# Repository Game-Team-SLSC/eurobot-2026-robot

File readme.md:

# Game Team's Eurobot 2026 Robot

## Hardware

### Architecture Diagram

```mermaid
graph LR
    %% SOURCES EXTERNES
    Batt((Batterie LiPo 4S))
    BAU[Bouton AU]

    %% PCB 1: LOGIC BOARD
    subgraph LB [Logic Board]
        direction TB
        MCU[ESP32-S3]
        Radio[Module Radio]
        Screen[Écran LCD]
        MCU --- Radio
        MCU --- Screen
    end

    %% PCB 2: POWER BOARD
    subgraph PB [Power Board]
        direction TB
        Prot[Protection Batterie]
        subgraph Drivers [Drivers Steppers]
            D_4x[4x Drivers]
        end
    end

    %% PCB 3: SERVO REGULATORS (Considéré comme un bloc PCB)
    subgraph Regs [Regulators Board]
        direction TB
        SR[2x 200W Servos]
        PR[1x 200W Pump Reg]
        Fan[1x Ventilateur]
    end

    %% PCB 4: ARM BOARD
    subgraph AB [Arm Board]
        direction TB
        PCA[3x PCA9685]
        Mos[4x MOSFET Pumps]
    end

    %% MATÉRIEL PHYSIQUE (Hors PCB)
    subgraph Mecanique [Éléments Mécaniques]
        Mots[4x Steppers]
        CN[Chasse-Neige]
        Bras[Bras & Pompes]
    end

    %% CONNEXIONS INTER-PCB (Puissance)
    Batt == "16.8V" ==> PB
    PB == "16.8V" ==> LB
    PB == "16.8V" ==> Regs
    Regs == "7V / 12V" ==> AB
    BAU -.-> PB
    AB -- PWM -->Regs

    %% CONNEXIONS INTER-PCB (Signaux)
    LB -- "SPI" --> PB
    LB -- "I2C Main" --> AB
    PB -- "Télémétrie" --> LB

    %% CONNEXIONS PCB VERS MÉCANIQUE
    PB == "Phases" ==> Mots
    AB -- "PWM" --> CN
    AB -- "Faisceau" --> Bras

    %% STYLES
    style LB fill:#f3e5f5,stroke:#7b1fa2,stroke-width:2px
    style PB fill:#fff9c4,stroke:#fbc02d,stroke-width:2px
    style Regs fill:#e1f5fe,stroke:#0288d1,stroke-width:2px
    style AB fill:#e8f5e9,stroke:#2e7d32,stroke-width:2px
```

### Power PCB

### Kinetic PCB

### Logic PCB

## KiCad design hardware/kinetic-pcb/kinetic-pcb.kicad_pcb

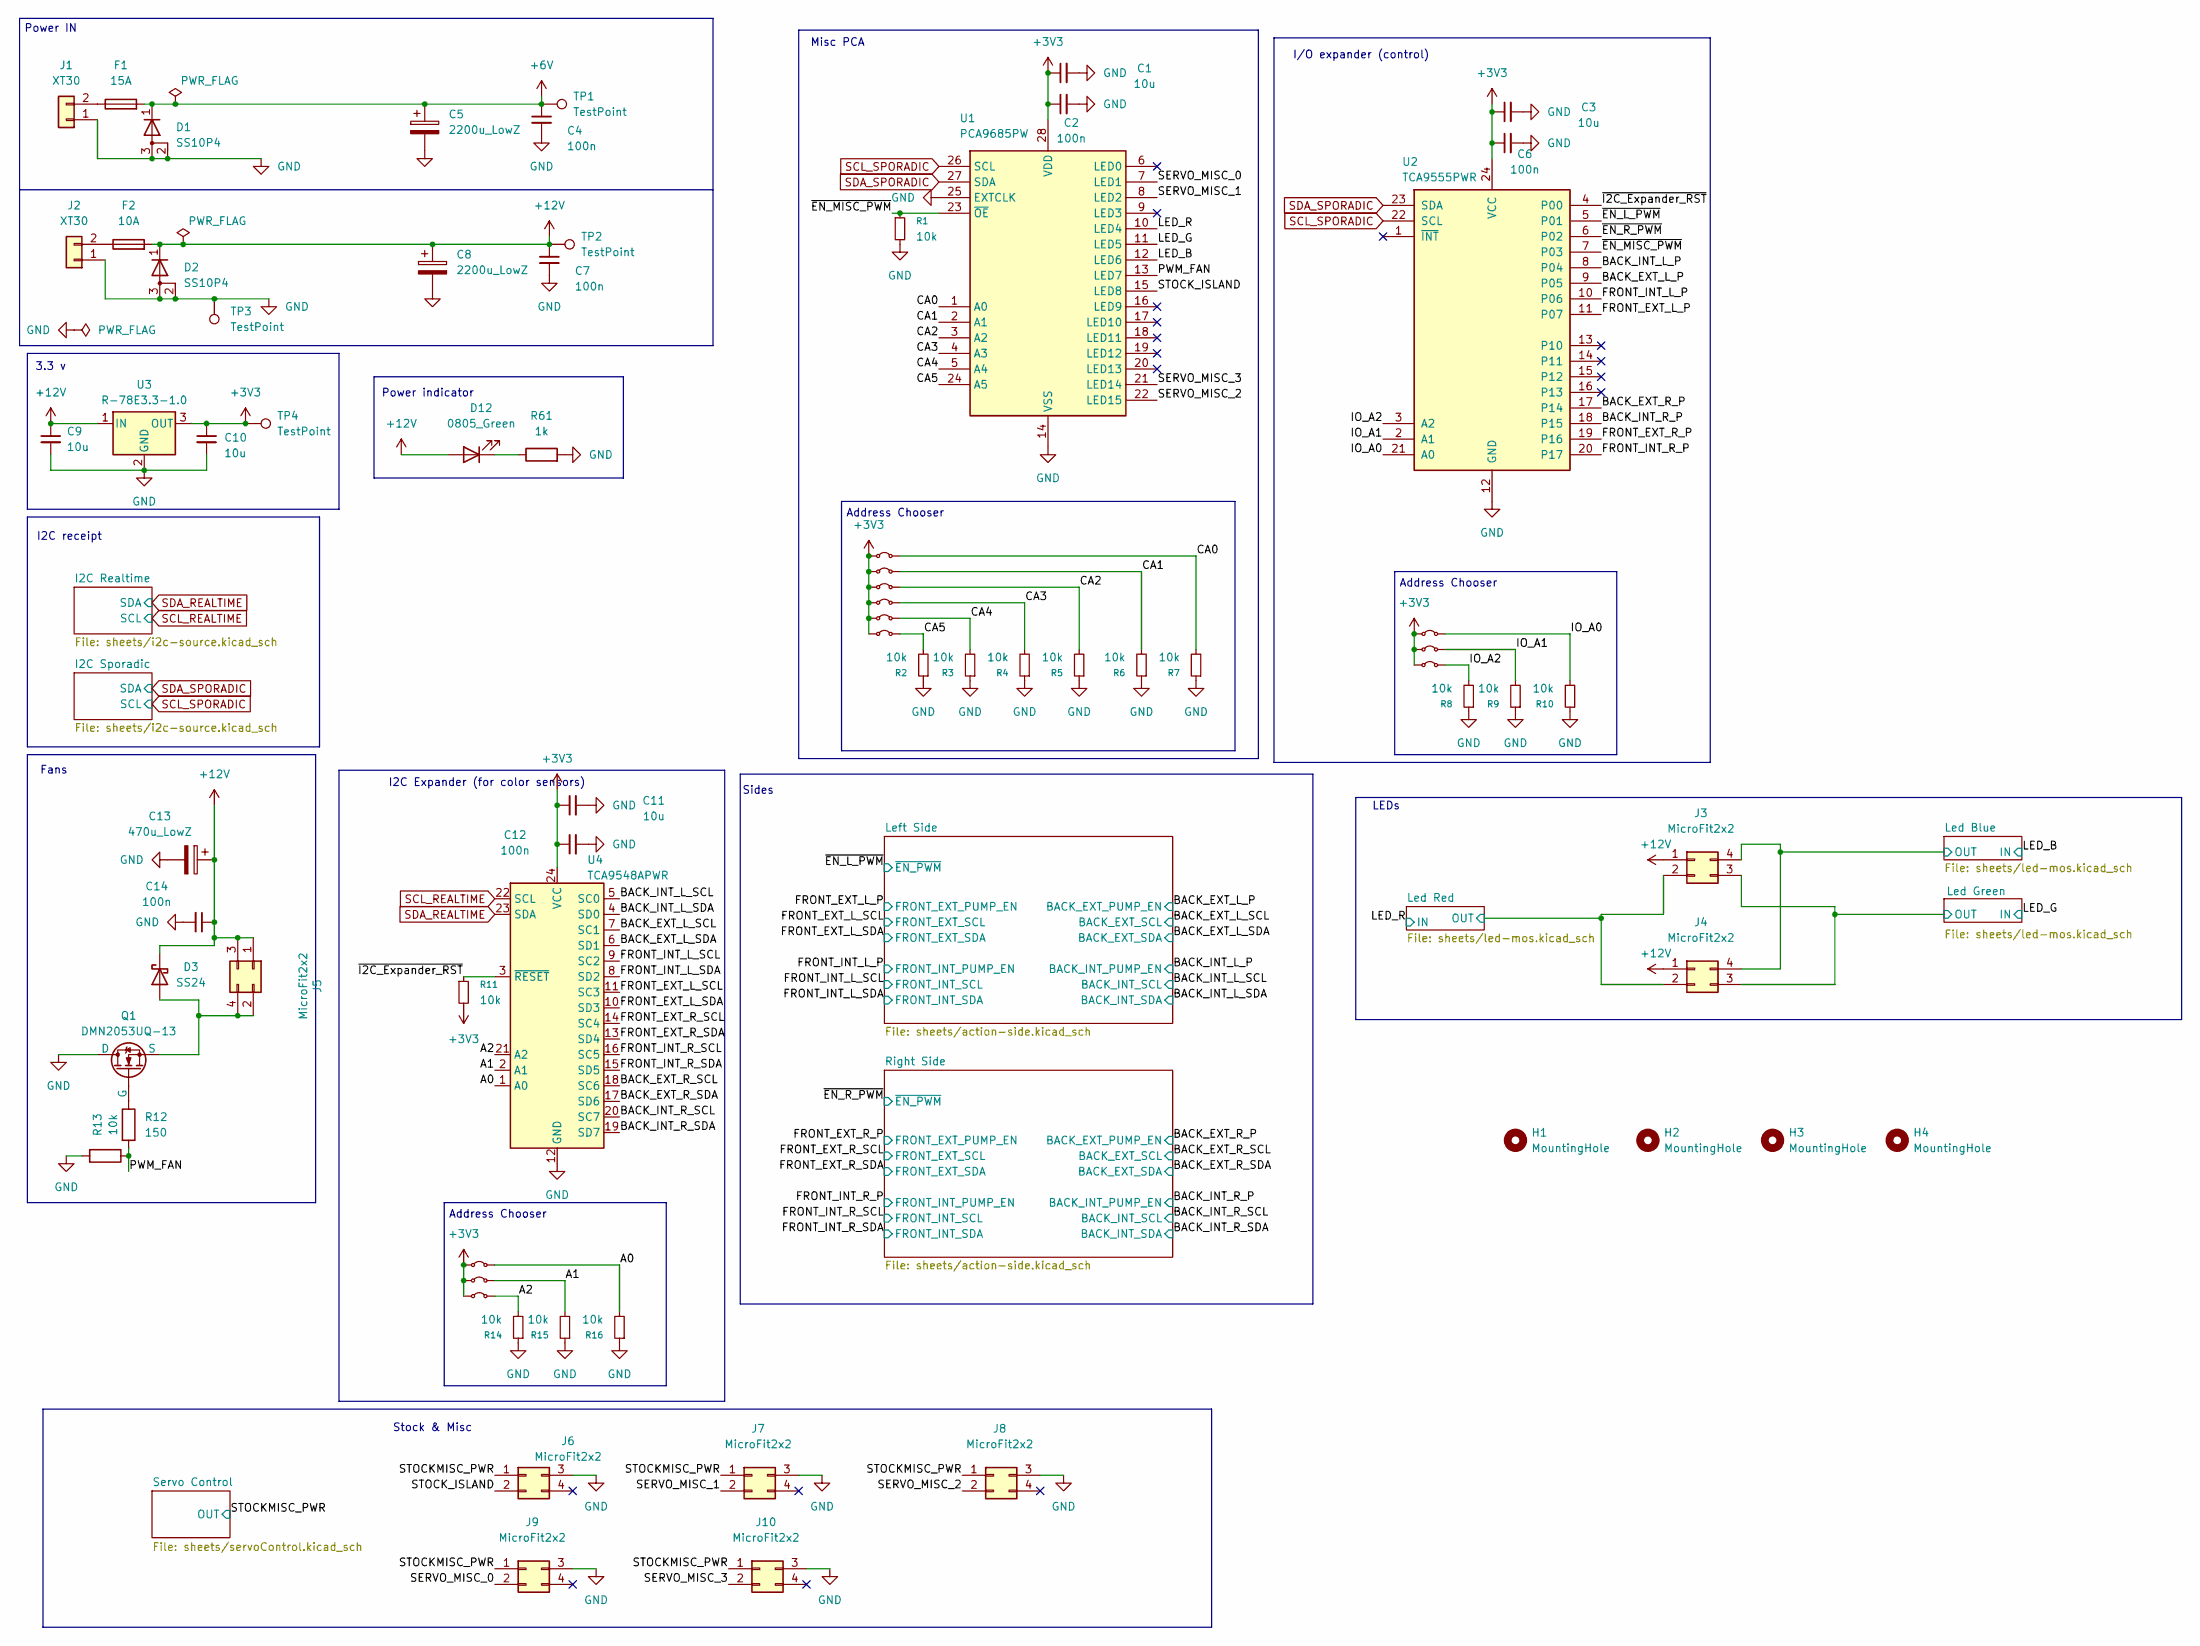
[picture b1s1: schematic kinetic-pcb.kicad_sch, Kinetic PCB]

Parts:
C1, C3, C9, C10, C11: 10u; C_0805_2012Metric_Pad1.18x1.45mm_HandSolder; MPN CL21A106KBYQNNE
C2, C4, C6, C7, C12, C14: 100n; C_0805_2012Metric_Pad1.18x1.45mm_HandSolder; MPN CL21B104KBCNNND
C5, C8: 2200u_LowZ; CP_Radial_D16.0mm_P7.50mm; MPN EEUFR1V222
C13: 470u_LowZ; CP_Radial_D10.0mm_P5.00mm; MPN EEU-FR1E471
D1, D2: SS10P4; SS10P4M387A; MPN SS10P4-M3/87A
D3: SS24; D_SMA_Handsoldering; MPN SS24S-E3/5AT
D12: 0805_Green; LED_0805_2012Metric_Pad1.15x1.40mm_HandSolder; MPN APA2106ZGCK
F1: 15A; Fuseholder_Cylinder-5x20mm_Schurter_0031_8201_Horizontal_Op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
F2: 10A; Fuseholder_Cylinder-5x20mm_Schurter_0031_8201_Horizontal_Op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
H1, H2, H3, H4: MountingHole; MountingHole_3.2mm_M3
J1, J2: XT30; AMASS_XT30U-M_1x02_P5.0mm_Vertical
J3, J4, J5, J6, J7, J8, J9, J10: MicroFit2x2; J_Wurth_WR-MPC3_66200421122; MPN 66200421122
NT1, NT2, NT3, NT4, NT5, NT6, NT7, NT8, NT9, NT10, NT11, NT12: Jumper_2_Bridged; TestPoint_2Pads_Pitch2.54mm_Drill0.8mm; MPN M7582-46
Q1: DMN2053UQ-13; SOT-23_Handsoldering-DMN2053UQ; MPN DMN2053UQ-13
R1, R2, R3, R4, R5, R6, R7, R8, R9, R10, R11, R13, R14, R15, R16: 10k; R_0805_2012Metric_Pad1.20x1.40mm_HandSolder; MPN CRCW080510K0FKEA
R12: 150; R_0805_2012Metric_Pad1.20x1.40mm_HandSolder; MPN CRCW0805150RFKEA
R61: 1k; R_0805_2012Metric_Pad1.20x1.40mm_HandSolder; MPN CRCW08051K00FKEA
TP1, TP2, TP3, TP4: TestPoint; TestPoint_THTPad_D2.0mm_Drill1.0mm
U1: PCA9685PW; TSSOP-28_4.4x9.7mm_P0.65mm; MPN PCA9685PW,118
U2: TCA9555PWR; TSSOP-24_4.4x7.8mm_P0.65mm; MPN TCA9555PWR
U3: R-78E3.3-1.0; Converter_DCDC_RECOM_R-78E-0.5_THT; MPN R-78E3.3-1.0
U4: TCA9548APWR; TSSOP-24_4.4x7.8mm_P0.65mm; MPN TCA9548APWR

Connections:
+3V3: C1.1, C2.1, C3.1, C6.1, C10.1, C11.1, C12.1, NT1.1 (A), NT2.1 (A), NT3.1 (A), NT4.1 (A), NT5.1 (A), NT6.1 (A), NT7.1 (A), NT8.1 (A), NT9.1 (A), NT10.1 (A), NT11.1 (A), NT12.1 (A), R11.2, TP4.1, U1.28 (VDD), U2.24 (VCC), U3.3 (OUT), U4.24 (VCC); also elsewhere on the board
+6V: C4.1, C5.1, D1.1 (K), F1.2, J6.1, J7.1, J8.1, J9.1, J10.1, TP1.1; also elsewhere on the board
+12V: C7.1, C8.1, C9.1, C13.1, C14.1, D2.1 (K), D3.1 (K), D12.2 (A), F2.2, J3.1, J4.1, J5.1, J5.3, TP2.1, U3.1 (IN); also elsewhere on the board
/A0: NT10.2 (B), R16.2, U4.1 (A0)
/A1: NT11.2 (B), R15.2, U4.2 (A1)
/A2: NT12.2 (B), R14.2, U4.21 (A2)
/BACK_EXT_L_P: U2.9 (P05); also elsewhere on the board
/BACK_EXT_L_SCL: U4.7 (SC1); also elsewhere on the board
/BACK_EXT_L_SDA: U4.6 (SD1); also elsewhere on the board
/BACK_EXT_R_P: U2.17 (P14); also elsewhere on the board
/BACK_EXT_R_SCL: U4.18 (SC6); also elsewhere on the board
/BACK_EXT_R_SDA: U4.17 (SD6); also elsewhere on the board
/BACK_INT_L_P: U2.8 (P04); also elsewhere on the board
/BACK_INT_L_SCL: U4.5 (SC0); also elsewhere on the board
/BACK_INT_L_SDA: U4.4 (SD0); also elsewhere on the board
/BACK_INT_R_P: U2.18 (P15); also elsewhere on the board
/BACK_INT_R_SCL: U4.20 (SC7); also elsewhere on the board
/BACK_INT_R_SDA: U4.19 (SD7); also elsewhere on the board
/CA0: NT1.2 (B), R7.2, U1.1 (A0)
/CA1: NT2.2 (B), R6.2, U1.2 (A1)
/CA2: NT3.2 (B), R5.2, U1.3 (A2)
/CA3: NT4.2 (B), R4.2, U1.4 (A3)
/CA4: NT5.2 (B), R3.2, U1.5 (A4)
/CA5: NT6.2 (B), R2.2, U1.24 (A5)
/FRONT_EXT_L_P: U2.11 (P07); also elsewhere on the board
/FRONT_EXT_L_SCL: U4.11 (SC3); also elsewhere on the board
/FRONT_EXT_L_SDA: U4.10 (SD3); also elsewhere on the board
/FRONT_EXT_R_P: U2.19 (P16); also elsewhere on the board
/FRONT_EXT_R_SCL: U4.14 (SC4); also elsewhere on the board
/FRONT_EXT_R_SDA: U4.13 (SD4); also elsewhere on the board
/FRONT_INT_L_P: U2.10 (P06); also elsewhere on the board
/FRONT_INT_L_SCL: U4.9 (SC2); also elsewhere on the board
/FRONT_INT_L_SDA: U4.8 (SD2); also elsewhere on the board
/FRONT_INT_R_P: U2.20 (P17); also elsewhere on the board
/FRONT_INT_R_SCL: U4.16 (SC5); also elsewhere on the board
/FRONT_INT_R_SDA: U4.15 (SD5); also elsewhere on the board
/IO_A0: NT7.2 (B), R10.2, U2.21 (A0)
/IO_A1: NT8.2 (B), R9.2, U2.2 (A1)
/IO_A2: NT9.2 (B), R8.2, U2.3 (A2)
/LED_B: U1.12 (LED6); also elsewhere on the board
/LED_G: U1.11 (LED5); also elsewhere on the board
/LED_R: U1.10 (LED4); also elsewhere on the board
/Led Blue/OUT: J3.4, J4.4; also elsewhere on the board
/Led Green/OUT: J3.3, J4.3; also elsewhere on the board
/Led Red/OUT: J3.2, J4.2; also elsewhere on the board
/PWM_FAN: R12.2, R13.1, U1.13 (LED7)
/SERVO_MISC_0: J9.2, U1.7 (LED1)
/SERVO_MISC_1: J7.2, U1.8 (LED2)
/SERVO_MISC_2: J8.2, U1.22 (LED15)
/SERVO_MISC_3: J10.2, U1.21 (LED14)
/STOCK_ISLAND: J6.2, U1.15 (LED8)
/~EN_L_PWM: U2.5 (P01); also elsewhere on the board
/~EN_MISC_PWM: R1.1, U1.23 (~OE), U2.7 (P03)
/~EN_R_PWM: U2.6 (P02); also elsewhere on the board
/~I2C_Expander_RST: R11.1, U2.4 (P00), U4.3 (~RESET)
GND: C1.2, C2.2, C3.2, C4.2, C5.2, C6.2, C7.2, C8.2, C9.2, C10.2, C11.2, C12.2, C13.2, C14.2, D1.2 (A), D1.3 (A), D2.2 (A), D2.3 (A), J1.1, J2.1, J6.3, J7.3, J8.3, J9.3, J10.3, Q1.1 (D), R1.2, R2.1, R3.1, R4.1, R5.1, R6.1, R7.1, R8.1, R9.1, R10.1, R13.2, R14.1, R15.1, R16.1, R61.2, TP3.1, U1.14 (VSS), U1.25 (EXTCLK), U2.12 (GND), U3.2 (GND), U4.12 (GND); also elsewhere on the board
unnamed: D3.2 (A), J5.2, J5.4, Q1.3 (S)
unnamed: D12.1 (K), R61.1
unnamed: F1.1, J1.2
unnamed: F2.1, J2.2
unnamed: Q1.2 (G), R12.1
SCL_REALTIME: U4.22 (SCL); also elsewhere on the board
SCL_SPORADIC: U1.26 (SCL), U2.22 (SCL); also elsewhere on the board
SDA_REALTIME: U4.23 (SDA); also elsewhere on the board
SDA_SPORADIC: U1.27 (SDA), U2.23 (SDA); also elsewhere on the board

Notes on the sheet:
Fans
Address Chooser
3.3 v
Sides
I2C Expander (for color sensors)
Stock & Misc
Power IN
Power indicator
I/O expander (control)
LEDs
Misc PCA
I2C receipt

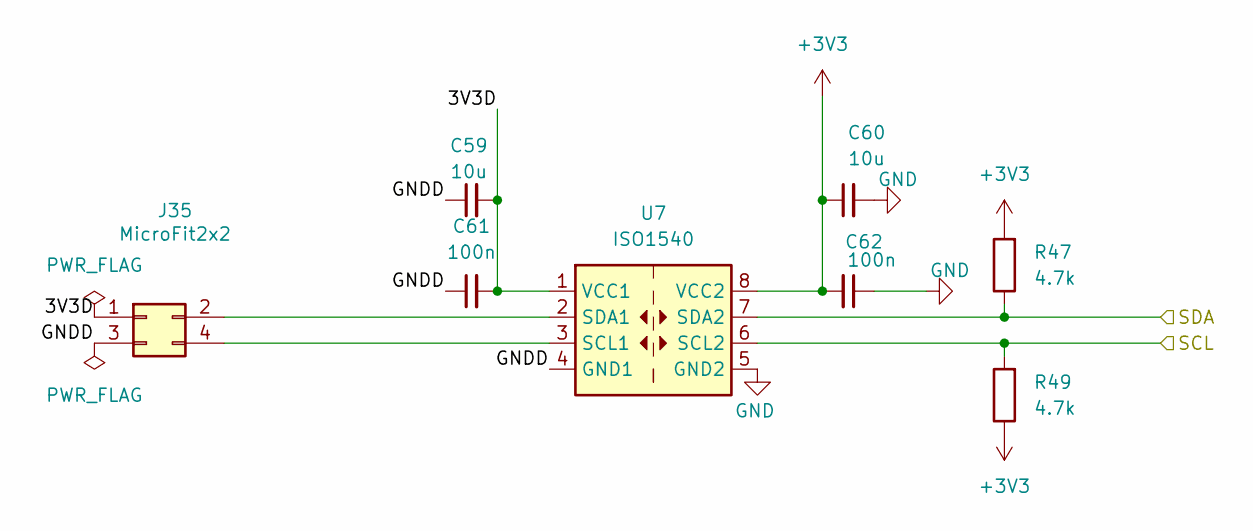
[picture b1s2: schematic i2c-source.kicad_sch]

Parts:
C59, C60: 10u; C_0805_2012Metric_Pad1.18x1.45mm_HandSolder; MPN CL21A106KBYQNNE
C61, C62: 100n; C_0805_2012Metric_Pad1.18x1.45mm_HandSolder; MPN CL21B104KBCNNND
J35: MicroFit2x2; J_Wurth_WR-MPC3_66200421122; MPN 66200421122
R47, R49: 4.7k; R_0805_2012Metric_Pad1.20x1.40mm_HandSolder; MPN CRCW08054K70FKEA
U7: ISO1540; SOIC-8_3.9x4.9mm_P1.27mm; MPN ISO1540DR

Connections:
+3V3: C60.1, C62.2, R47.2, R49.1, U7.8 (VCC2); also elsewhere on the board
/I2C Sporadic/3V3D: C59.2, C61.2, J35.1, U7.1 (VCC1)
/I2C Sporadic/GNDD: C59.1, C61.1, J35.3, U7.4 (GND1)
GND: C60.2, C62.1, U7.5 (GND2); also elsewhere on the board
unnamed: J35.2, U7.2 (SDA1)
unnamed: J35.4, U7.3 (SCL1)
SCL_SPORADIC: R49.2, U7.6 (SCL2); also elsewhere on the board
SDA_SPORADIC: R47.1, U7.7 (SDA2); also elsewhere on the board

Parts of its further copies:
C63, C64: 10u; C_0805_2012Metric_Pad1.18x1.45mm_HandSolder; MPN CL21A106KBYQNNE
C65, C66: 100n; C_0805_2012Metric_Pad1.18x1.45mm_HandSolder; MPN CL21B104KBCNNND
J36: MicroFit2x2; J_Wurth_WR-MPC3_66200421122; MPN 66200421122
R54, R56: 4.7k; R_0805_2012Metric_Pad1.20x1.40mm_HandSolder; MPN CRCW08054K70FKEA
U8: ISO1540; SOIC-8_3.9x4.9mm_P1.27mm; MPN ISO1540DR

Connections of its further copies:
+3V3: C64.1, C66.2, R54.2, R56.1, U8.8 (VCC2); also elsewhere on the board
/I2C Realtime/3V3D: C63.2, C65.2, J36.1, U8.1 (VCC1)
/I2C Realtime/GNDD: C63.1, C65.1, J36.3, U8.4 (GND1)
GND: C64.2, C66.1, U8.5 (GND2); also elsewhere on the board
unnamed: J36.2, U8.2 (SDA1)
unnamed: J36.4, U8.3 (SCL1)
SCL_REALTIME: R56.2, U8.6 (SCL2); also elsewhere on the board
SDA_REALTIME: R54.1, U8.7 (SDA2); also elsewhere on the board

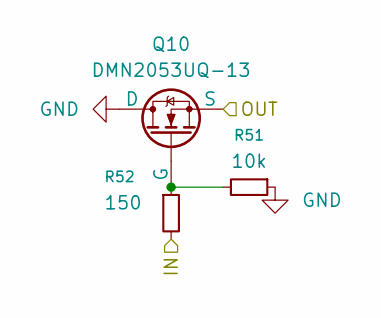
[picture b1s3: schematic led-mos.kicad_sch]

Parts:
Q10: DMN2053UQ-13; SOT-23_Handsoldering-DMN2053UQ; MPN DMN2053UQ-13
R51: 10k; R_0805_2012Metric_Pad1.20x1.40mm_HandSolder; MPN CRCW080510K0FKEA
R52: 150; R_0805_2012Metric_Pad1.20x1.40mm_HandSolder; MPN CRCW0805150RFKEA

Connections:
/LED_G: R52.2; also elsewhere on the board
/Led Green/OUT: Q10.3 (S); also elsewhere on the board
GND: Q10.1 (D), R51.1; also elsewhere on the board
unnamed: Q10.2 (G), R51.2, R52.1

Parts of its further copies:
Q11, Q12: DMN2053UQ-13; SOT-23_Handsoldering-DMN2053UQ; MPN DMN2053UQ-13
R57, R59: 10k; R_0805_2012Metric_Pad1.20x1.40mm_HandSolder; MPN CRCW080510K0FKEA
R58, R60: 150; R_0805_2012Metric_Pad1.20x1.40mm_HandSolder; MPN CRCW0805150RFKEA

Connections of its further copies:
/LED_B: R58.2; also elsewhere on the board
/LED_R: R60.2; also elsewhere on the board
/Led Blue/OUT: Q11.3 (S); also elsewhere on the board
/Led Red/OUT: Q12.3 (S); also elsewhere on the board
GND: Q11.1 (D), Q12.1 (D), R57.1, R59.1; also elsewhere on the board
unnamed: Q11.2 (G), R57.2, R58.1
unnamed: Q12.2 (G), R59.2, R60.1

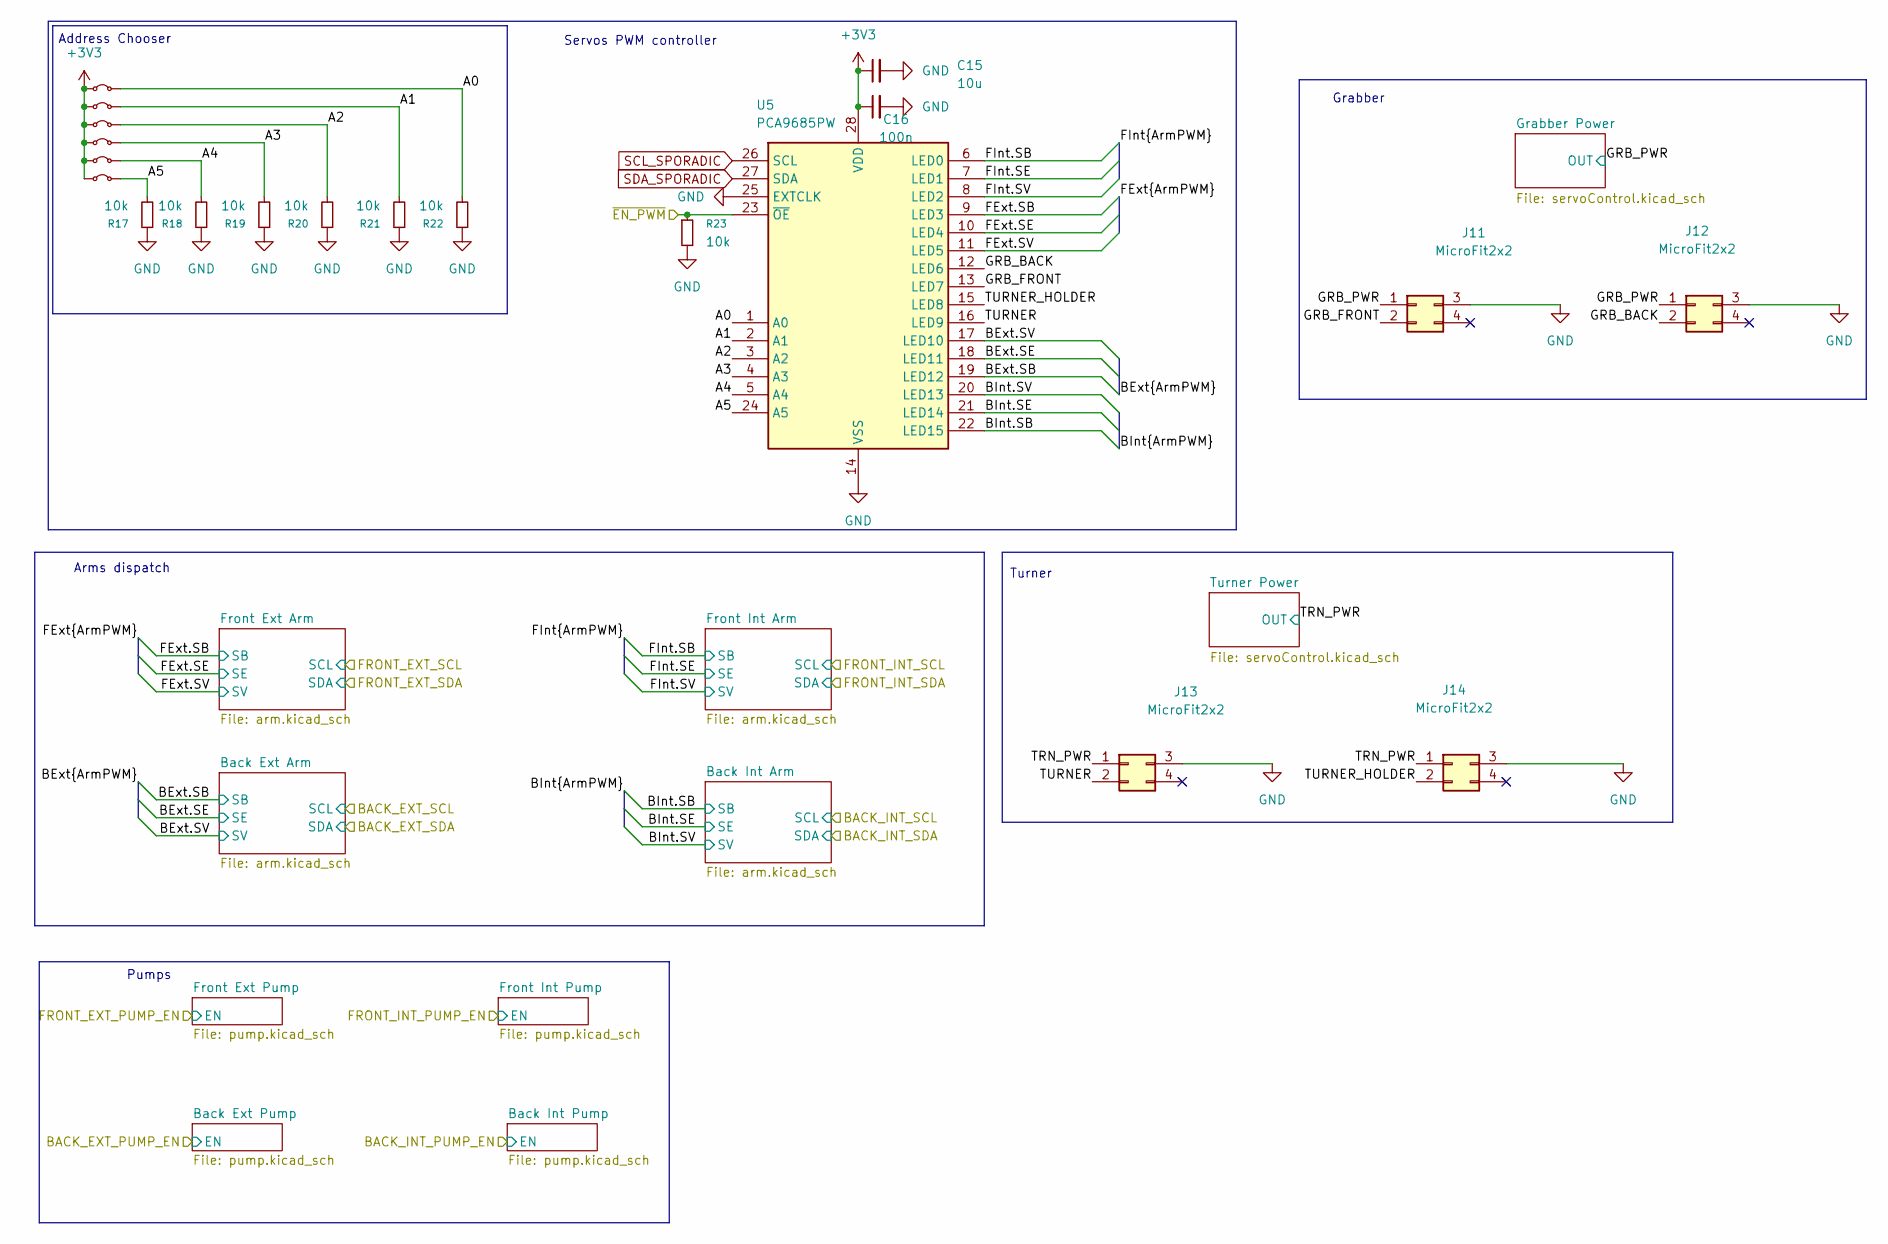
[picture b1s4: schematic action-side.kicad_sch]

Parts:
C15: 10u; C_0805_2012Metric_Pad1.18x1.45mm_HandSolder; MPN CL21A106KBYQNNE
C16: 100n; C_0805_2012Metric_Pad1.18x1.45mm_HandSolder; MPN CL21B104KBCNNND
J11, J12, J13, J14: MicroFit2x2; J_Wurth_WR-MPC3_66200421122; MPN 66200421122
NT13, NT14, NT15, NT16, NT17, NT18: Jumper_2_Bridged; TestPoint_2Pads_Pitch2.54mm_Drill0.8mm; MPN M7582-46
R17, R18, R19, R20, R21, R22, R23: 10k; R_0805_2012Metric_Pad1.20x1.40mm_HandSolder; MPN CRCW080510K0FKEA
U5: PCA9685PW; TSSOP-28_4.4x9.7mm_P0.65mm; MPN PCA9685PW,118

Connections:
+3V3: C15.1, C16.1, NT13.1 (A), NT14.1 (A), NT15.1 (A), NT16.1 (A), NT17.1 (A), NT18.1 (A), U5.28 (VDD); also elsewhere on the board
+6V: J11.1, J12.1, J13.1, J14.1; also elsewhere on the board
/Left Side/A0: NT13.2 (B), R22.2, U5.1 (A0)
/Left Side/A1: NT14.2 (B), R21.2, U5.2 (A1)
/Left Side/A2: NT15.2 (B), R20.2, U5.3 (A2)
/Left Side/A3: NT16.2 (B), R19.2, U5.4 (A3)
/Left Side/A4: NT17.2 (B), R18.2, U5.5 (A4)
/Left Side/A5: NT18.2 (B), R17.2, U5.24 (A5)
/Left Side/BExt.SB: U5.19 (LED12); also elsewhere on the board
/Left Side/BExt.SE: U5.18 (LED11); also elsewhere on the board
/Left Side/BExt.SV: U5.17 (LED10); also elsewhere on the board
/Left Side/BInt.SB: U5.22 (LED15); also elsewhere on the board
/Left Side/BInt.SE: U5.21 (LED14); also elsewhere on the board
/Left Side/BInt.SV: U5.20 (LED13); also elsewhere on the board
/Left Side/FExt.SB: U5.9 (LED3); also elsewhere on the board
/Left Side/FExt.SE: U5.10 (LED4); also elsewhere on the board
/Left Side/FExt.SV: U5.11 (LED5); also elsewhere on the board
/Left Side/FInt.SB: U5.6 (LED0); also elsewhere on the board
/Left Side/FInt.SE: U5.7 (LED1); also elsewhere on the board
/Left Side/FInt.SV: U5.8 (LED2); also elsewhere on the board
/Left Side/GRB_BACK: J12.2, U5.12 (LED6)
/Left Side/GRB_FRONT: J11.2, U5.13 (LED7)
/Left Side/TURNER: J13.2, U5.16 (LED9)
/Left Side/TURNER_HOLDER: J14.2, U5.15 (LED8)
/~EN_L_PWM: R23.1, U5.23 (~OE); also elsewhere on the board
GND: C15.2, C16.2, J11.3, J12.3, J13.3, J14.3, R17.1, R18.1, R19.1, R20.1, R21.1, R22.1, R23.2, U5.14 (VSS), U5.25 (EXTCLK); also elsewhere on the board
SCL_SPORADIC: U5.26 (SCL); also elsewhere on the board
SDA_SPORADIC: U5.27 (SDA); also elsewhere on the board

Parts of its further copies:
C21: 10u; C_0805_2012Metric_Pad1.18x1.45mm_HandSolder; MPN CL21A106KBYQNNE
C22: 100n; C_0805_2012Metric_Pad1.18x1.45mm_HandSolder; MPN CL21B104KBCNNND
J17, J18, J19, J20: MicroFit2x2; J_Wurth_WR-MPC3_66200421122; MPN 66200421122
NT19, NT20, NT21, NT22, NT23, NT24: Jumper_2_Bridged; TestPoint_2Pads_Pitch2.54mm_Drill0.8mm; MPN M7582-46
R26, R27, R28, R29, R30, R31, R32: 10k; R_0805_2012Metric_Pad1.20x1.40mm_HandSolder; MPN CRCW080510K0FKEA
U6: PCA9685PW; TSSOP-28_4.4x9.7mm_P0.65mm; MPN PCA9685PW,118

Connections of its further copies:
+3V3: C21.1, C22.1, NT19.1 (A), NT20.1 (A), NT21.1 (A), NT22.1 (A), NT23.1 (A), NT24.1 (A), U6.28 (VDD); also elsewhere on the board
+6V: J17.1, J18.1, J19.1, J20.1; also elsewhere on the board
/Right Side/A0: NT19.2 (B), R31.2, U6.1 (A0)
/Right Side/A1: NT20.2 (B), R30.2, U6.2 (A1)
/Right Side/A2: NT21.2 (B), R29.2, U6.3 (A2)
/Right Side/A3: NT22.2 (B), R28.2, U6.4 (A3)
/Right Side/A4: NT23.2 (B), R27.2, U6.5 (A4)
/Right Side/A5: NT24.2 (B), R26.2, U6.24 (A5)
/Right Side/BExt.SB: U6.19 (LED12); also elsewhere on the board
/Right Side/BExt.SE: U6.18 (LED11); also elsewhere on the board
/Right Side/BExt.SV: U6.17 (LED10); also elsewhere on the board
/Right Side/BInt.SB: U6.22 (LED15); also elsewhere on the board
/Right Side/BInt.SE: U6.21 (LED14); also elsewhere on the board
/Right Side/BInt.SV: U6.20 (LED13); also elsewhere on the board
/Right Side/FExt.SB: U6.9 (LED3); also elsewhere on the board
/Right Side/FExt.SE: U6.10 (LED4); also elsewhere on the board
/Right Side/FExt.SV: U6.11 (LED5); also elsewhere on the board
/Right Side/FInt.SB: U6.6 (LED0); also elsewhere on the board
/Right Side/FInt.SE: U6.7 (LED1); also elsewhere on the board
/Right Side/FInt.SV: U6.8 (LED2); also elsewhere on the board
/Right Side/GRB_BACK: J18.2, U6.12 (LED6)
/Right Side/GRB_FRONT: J17.2, U6.13 (LED7)
/Right Side/TURNER: J19.2, U6.16 (LED9)
/Right Side/TURNER_HOLDER: J20.2, U6.15 (LED8)
/~EN_R_PWM: R32.1, U6.23 (~OE); also elsewhere on the board
GND: C21.2, C22.2, J17.3, J18.3, J19.3, J20.3, R26.1, R27.1, R28.1, R29.1, R30.1, R31.1, R32.2, U6.14 (VSS), U6.25 (EXTCLK); also elsewhere on the board
SCL_SPORADIC: U6.26 (SCL); also elsewhere on the board
SDA_SPORADIC: U6.27 (SDA); also elsewhere on the board

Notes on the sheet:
Address Chooser
Grabber
Arms dispatch
Pumps
Turner
Servos PWM controller

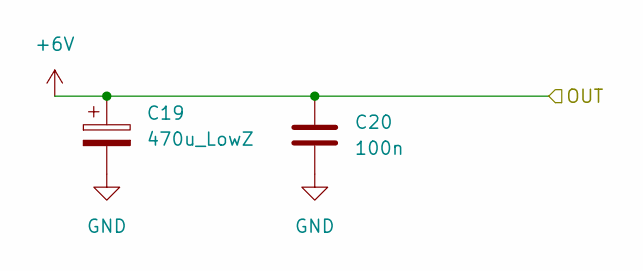
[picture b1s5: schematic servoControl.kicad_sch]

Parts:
C19: 470u_LowZ; CP_Radial_D10.0mm_P5.00mm; MPN EEU-FR1E471
C20: 100n; C_0805_2012Metric_Pad1.18x1.45mm_HandSolder; MPN CL21B104KBCNNND

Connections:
+6V: C19.1, C20.1; also elsewhere on the board
GND: C19.2, C20.2; also elsewhere on the board

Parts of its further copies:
C23, C25, C29, C41, C43, C45, C47, C49, C53, C55, C57, C67: 470u_LowZ; CP_Radial_D10.0mm_P5.00mm; MPN EEU-FR1E471
C24, C26, C30, C42, C44, C46, C48, C50, C54, C56, C58, C68: 100n; C_0805_2012Metric_Pad1.18x1.45mm_HandSolder; MPN CL21B104KBCNNND

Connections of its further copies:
+6V: C23.1, C24.1, C25.1, C26.1, C29.1, C30.1, C41.1, C42.1, C43.1, C44.1, C45.1, C46.1, C47.1, C48.1, C49.1, C50.1, C53.1, C54.1, C55.1, C56.1, C57.1, C58.1, C67.1, C68.1; also elsewhere on the board
GND: C23.2, C24.2, C25.2, C26.2, C29.2, C30.2, C41.2, C42.2, C43.2, C44.2, C45.2, C46.2, C47.2, C48.2, C49.2, C50.2, C53.2, C54.2, C55.2, C56.2, C57.2, C58.2, C67.2, C68.2; also elsewhere on the board

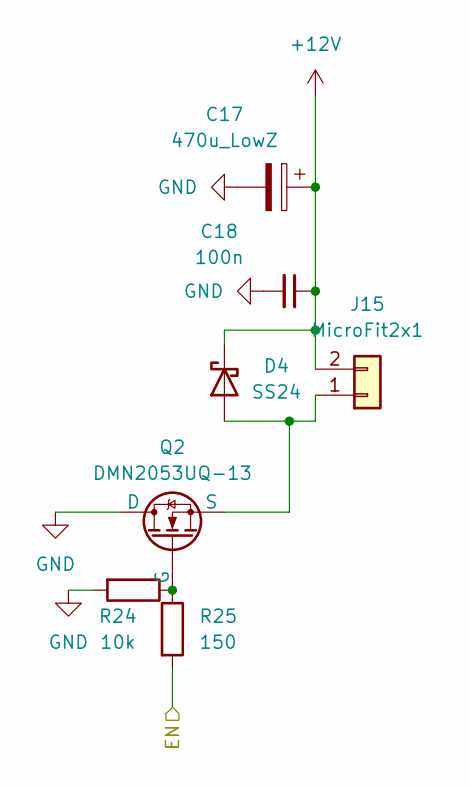
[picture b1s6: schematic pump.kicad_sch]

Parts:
C17: 470u_LowZ; CP_Radial_D10.0mm_P5.00mm; MPN EEU-FR1E471
C18: 100n; C_0805_2012Metric_Pad1.18x1.45mm_HandSolder; MPN CL21B104KBCNNND
D4: SS24; D_SMA_Handsoldering; MPN SS24S-E3/5AT
J15: MicroFit2x1; J_Wurth_WR-MPC3_66200211122; MPN 66200211122
Q2: DMN2053UQ-13; SOT-23_Handsoldering-DMN2053UQ; MPN DMN2053UQ-13
R24: 10k; R_0805_2012Metric_Pad1.20x1.40mm_HandSolder; MPN CRCW080510K0FKEA
R25: 150; R_0805_2012Metric_Pad1.20x1.40mm_HandSolder; MPN CRCW0805150RFKEA

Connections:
+12V: C17.1, C18.1, D4.1 (K), J15.2; also elsewhere on the board
/BACK_INT_L_P: R25.2; also elsewhere on the board
GND: C17.2, C18.2, Q2.1 (D), R24.2; also elsewhere on the board
unnamed: D4.2 (A), J15.1, Q2.3 (S)
unnamed: Q2.2 (G), R24.1, R25.1

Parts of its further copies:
C27, C31, C33, C35, C37, C39, C51: 470u_LowZ; CP_Radial_D10.0mm_P5.00mm; MPN EEU-FR1E471
C28, C32, C34, C36, C38, C40, C52: 100n; C_0805_2012Metric_Pad1.18x1.45mm_HandSolder; MPN CL21B104KBCNNND
D5, D6, D7, D8, D9, D10, D11: SS24; D_SMA_Handsoldering; MPN SS24S-E3/5AT
J23, J24, J25, J26, J27, J28, J33: MicroFit2x1; J_Wurth_WR-MPC3_66200211122; MPN 66200211122
Q3, Q4, Q5, Q6, Q7, Q8, Q9: DMN2053UQ-13; SOT-23_Handsoldering-DMN2053UQ; MPN DMN2053UQ-13
R33, R35, R37, R39, R41, R43, R45: 10k; R_0805_2012Metric_Pad1.20x1.40mm_HandSolder; MPN CRCW080510K0FKEA
R34, R36, R38, R40, R42, R44, R46: 150; R_0805_2012Metric_Pad1.20x1.40mm_HandSolder; MPN CRCW0805150RFKEA

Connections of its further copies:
+12V: C27.1, C28.1, C31.1, C32.1, C33.1, C34.1, C35.1, C36.1, C37.1, C38.1, C39.1, C40.1, C51.1, C52.1, D5.1 (K), D6.1 (K), D7.1 (K), D8.1 (K), D9.1 (K), D10.1 (K), D11.1 (K), J23.2, J24.2, J25.2, J26.2, J27.2, J28.2, J33.2; also elsewhere on the board
/BACK_EXT_L_P: R36.2; also elsewhere on the board
/BACK_EXT_R_P: R40.2; also elsewhere on the board
/BACK_INT_R_P: R44.2; also elsewhere on the board
/FRONT_EXT_L_P: R46.2; also elsewhere on the board
/FRONT_EXT_R_P: R42.2; also elsewhere on the board
/FRONT_INT_L_P: R34.2; also elsewhere on the board
/FRONT_INT_R_P: R38.2; also elsewhere on the board
GND: C27.2, C28.2, C31.2, C32.2, C33.2, C34.2, C35.2, C36.2, C37.2, C38.2, C39.2, C40.2, C51.2, C52.2, Q3.1 (D), Q4.1 (D), Q5.1 (D), Q6.1 (D), Q7.1 (D), Q8.1 (D), Q9.1 (D), R33.2, R35.2, R37.2, R39.2, R41.2, R43.2, R45.2; also elsewhere on the board
unnamed: D5.2 (A), J23.1, Q3.3 (S)
unnamed: D6.2 (A), J24.1, Q4.3 (S)
unnamed: D7.2 (A), J25.1, Q5.3 (S)
unnamed: D8.2 (A), J26.1, Q6.3 (S)
unnamed: D9.2 (A), J27.1, Q7.3 (S)
unnamed: D10.2 (A), J28.1, Q8.3 (S)
unnamed: D11.2 (A), J33.1, Q9.3 (S)
unnamed: Q3.2 (G), R33.1, R34.1
unnamed: Q4.2 (G), R35.1, R36.1
unnamed: Q5.2 (G), R37.1, R38.1
unnamed: Q6.2 (G), R39.1, R40.1
unnamed: Q7.2 (G), R41.1, R42.1
unnamed: Q8.2 (G), R43.1, R44.1
unnamed: Q9.2 (G), R45.1, R46.1

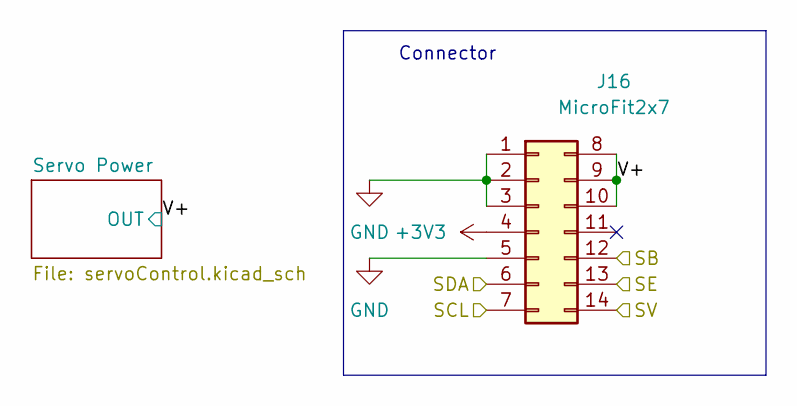
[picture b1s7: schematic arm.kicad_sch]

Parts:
J16: MicroFit2x7; J_Wurth_WR-MPC3_66201421122; MPN 43045-1412

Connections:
+3V3: J16.4; also elsewhere on the board
+6V: J16.8, J16.9, J16.10; also elsewhere on the board
/BACK_EXT_L_SCL: J16.7; also elsewhere on the board
/BACK_EXT_L_SDA: J16.6; also elsewhere on the board
/Left Side/BExt.SB: J16.12; also elsewhere on the board
/Left Side/BExt.SE: J16.13; also elsewhere on the board
/Left Side/BExt.SV: J16.14; also elsewhere on the board
GND: J16.1, J16.2, J16.3, J16.5; also elsewhere on the board

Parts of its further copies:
J21, J22, J29, J30, J31, J32, J34: MicroFit2x7; J_Wurth_WR-MPC3_66201421122; MPN 43045-1412

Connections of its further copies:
+3V3: J21.4, J22.4, J29.4, J30.4, J31.4, J32.4, J34.4; also elsewhere on the board
+6V: J21.8, J21.9, J21.10, J22.8, J22.9, J22.10, J29.8, J29.9, J29.10, J30.8, J30.9, J30.10, J31.8, J31.9, J31.10, J32.8, J32.9, J32.10, J34.8, J34.9, J34.10; also elsewhere on the board
/BACK_EXT_R_SCL: J22.7; also elsewhere on the board
/BACK_EXT_R_SDA: J22.6; also elsewhere on the board
/BACK_INT_L_SCL: J30.7; also elsewhere on the board
/BACK_INT_L_SDA: J30.6; also elsewhere on the board
/BACK_INT_R_SCL: J34.7; also elsewhere on the board
/BACK_INT_R_SDA: J34.6; also elsewhere on the board
/FRONT_EXT_L_SCL: J32.7; also elsewhere on the board
/FRONT_EXT_L_SDA: J32.6; also elsewhere on the board
/FRONT_EXT_R_SCL: J29.7; also elsewhere on the board
/FRONT_EXT_R_SDA: J29.6; also elsewhere on the board
/FRONT_INT_L_SCL: J21.7; also elsewhere on the board
/FRONT_INT_L_SDA: J21.6; also elsewhere on the board
/FRONT_INT_R_SCL: J31.7; also elsewhere on the board
/FRONT_INT_R_SDA: J31.6; also elsewhere on the board
/Left Side/BInt.SB: J30.12; also elsewhere on the board
/Left Side/BInt.SE: J30.13; also elsewhere on the board
/Left Side/BInt.SV: J30.14; also elsewhere on the board
/Left Side/FExt.SB: J32.12; also elsewhere on the board
/Left Side/FExt.SE: J32.13; also elsewhere on the board
/Left Side/FExt.SV: J32.14; also elsewhere on the board
/Left Side/FInt.SB: J21.12; also elsewhere on the board
/Left Side/FInt.SE: J21.13; also elsewhere on the board
/Left Side/FInt.SV: J21.14; also elsewhere on the board
/Right Side/BExt.SB: J22.12; also elsewhere on the board
/Right Side/BExt.SE: J22.13; also elsewhere on the board
/Right Side/BExt.SV: J22.14; also elsewhere on the board
/Right Side/BInt.SB: J34.12; also elsewhere on the board
/Right Side/BInt.SE: J34.13; also elsewhere on the board
/Right Side/BInt.SV: J34.14; also elsewhere on the board
/Right Side/FExt.SB: J29.12; also elsewhere on the board
/Right Side/FExt.SE: J29.13; also elsewhere on the board
/Right Side/FExt.SV: J29.14; also elsewhere on the board
/Right Side/FInt.SB: J31.12; also elsewhere on the board
/Right Side/FInt.SE: J31.13; also elsewhere on the board
/Right Side/FInt.SV: J31.14; also elsewhere on the board
GND: J21.1, J21.2, J21.3, J21.5, J22.1, J22.2, J22.3, J22.5, J29.1, J29.2, J29.3, J29.5, J30.1, J30.2, J30.3, J30.5, J31.1, J31.2, J31.3, J31.5, J32.1, J32.2, J32.3, J32.5, J34.1, J34.2, J34.3, J34.5; also elsewhere on the board

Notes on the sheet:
Connector

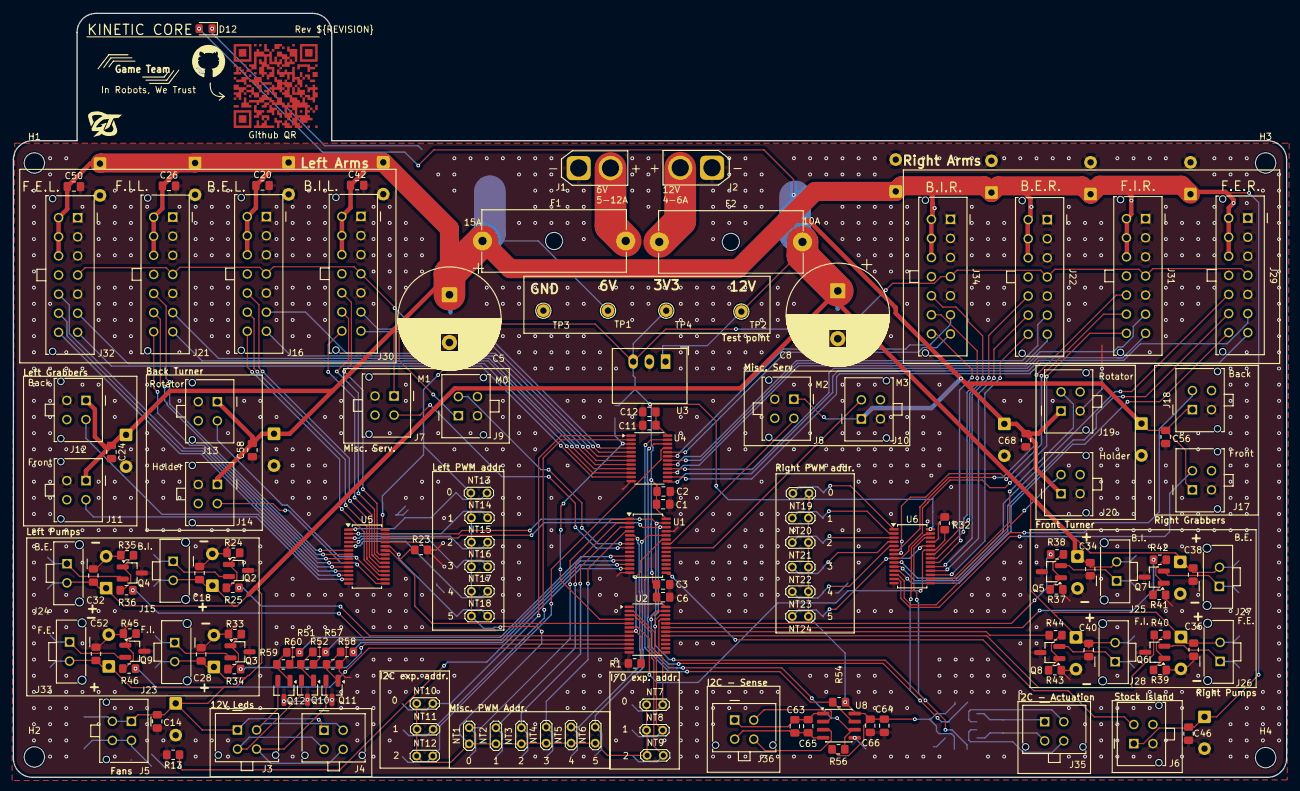
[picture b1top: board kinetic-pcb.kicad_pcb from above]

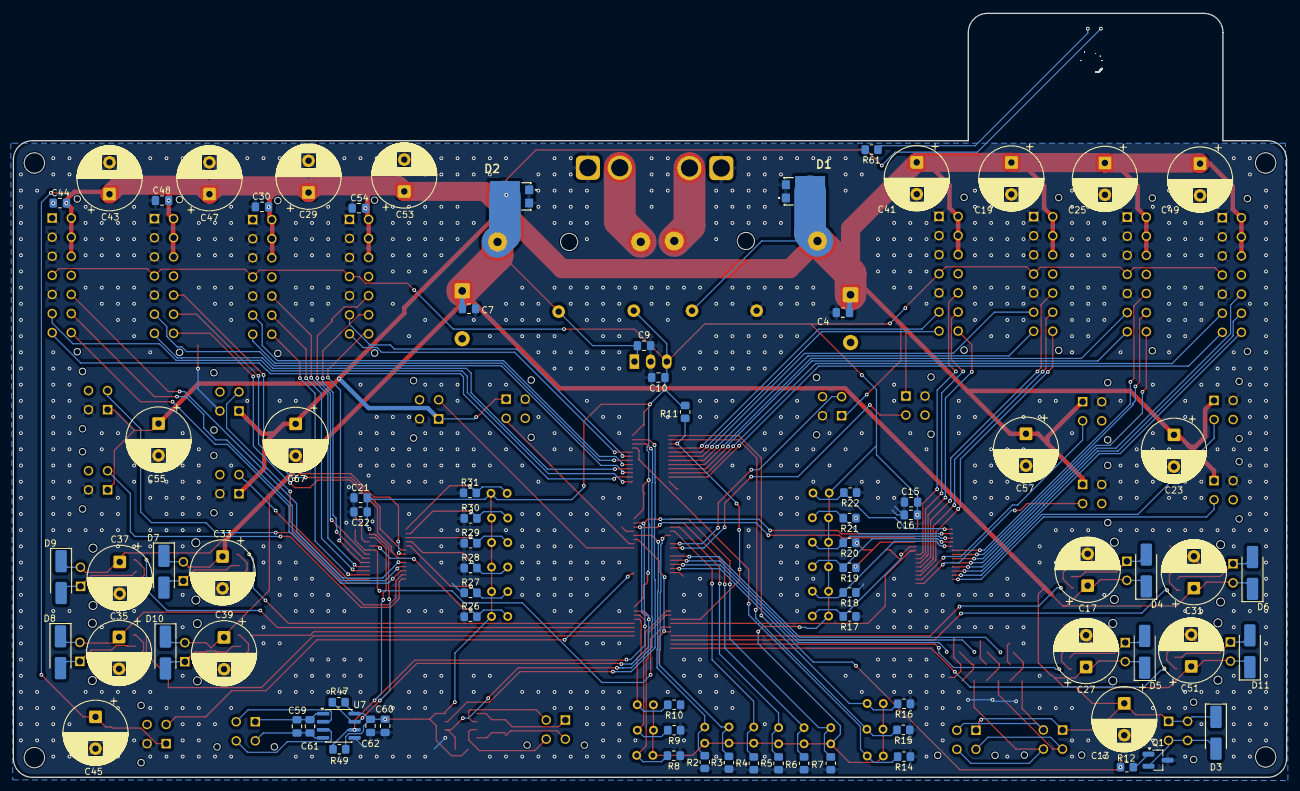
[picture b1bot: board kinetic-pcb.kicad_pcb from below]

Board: 2 copper layers, 200.0 x 120.0 mm, 228 parts (80 on the bottom side), 136 nets.

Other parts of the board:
QR*****: Github QR
